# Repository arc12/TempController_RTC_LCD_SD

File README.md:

Multiple DS18B20 temperature sensors with LCD display, SD card logging, remote control via Serial/USB, real time clock, and up to control an output.

Intended for compilation in Atmel Studio and deployment on a custom ATMega328 based circuit. See source code for notes on use with Arduino IDE.

Various library dependencies not in github yet (will be separate repos). See *.atsln

The idea of this is to have 3 temp sensors: one in a well inside the beer (5 gallon bucket), one inside a ply-wood box (contains a heater pad and the bucket), and one in the outside room. Logging temperature for all three will give an idea of the thermal properties of the assembly and of the heat produced by fermentation. In the first instance, a very simple control rule will be used, taking only the temperature from in the wort and testing for a min temperature with fixed hysteresis. See the MS Word Doc.

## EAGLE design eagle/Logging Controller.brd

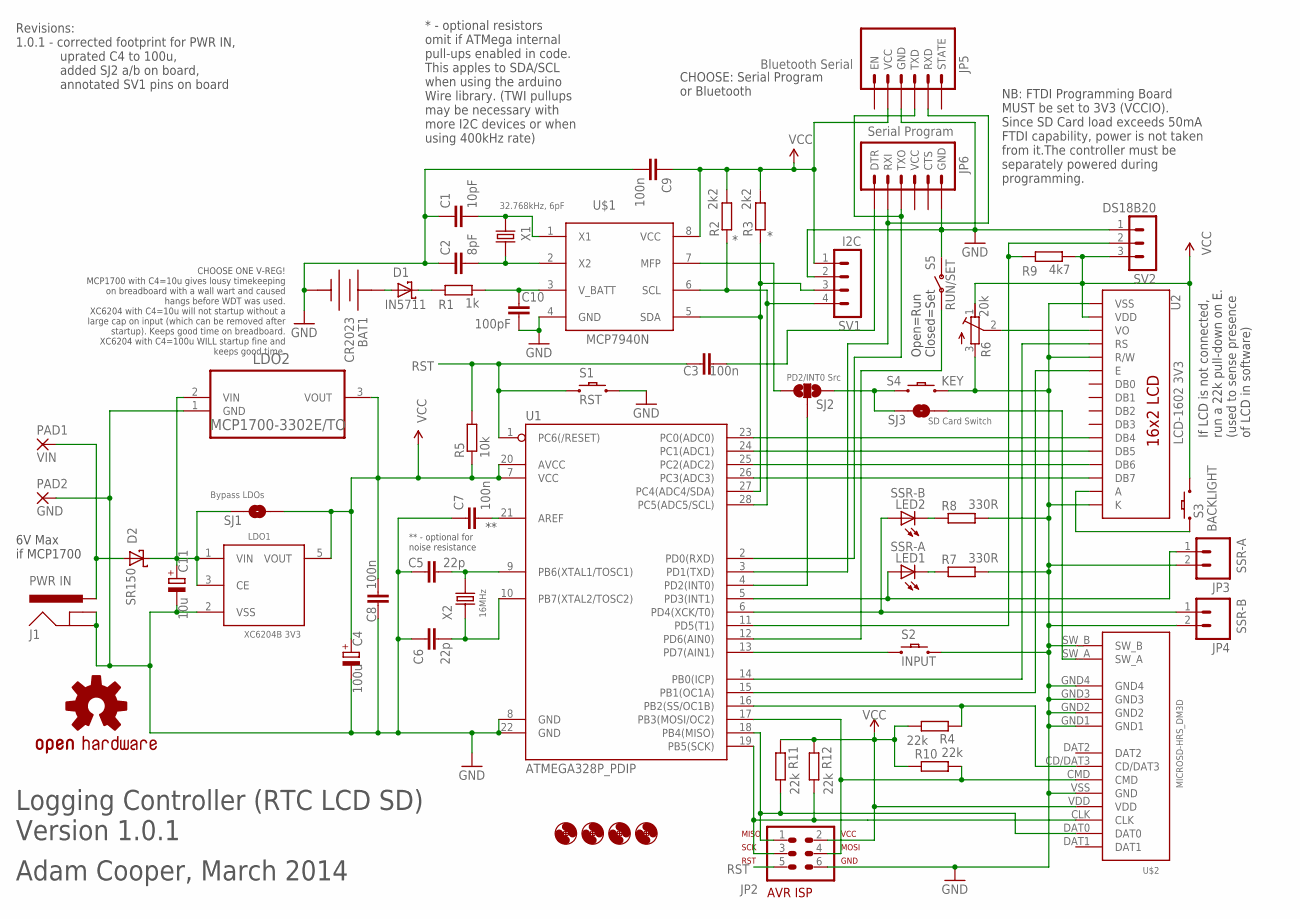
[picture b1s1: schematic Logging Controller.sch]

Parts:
BAT1: CR2023; KEYSTONE3003
C1: 10pF; C025-024X044
C2: 8pF; C025-024X044
C3, C7, C8, C9: 100n; C025-024X044
C4: 100u; E2,5-5
C5, C6: 22p; C025-024X044
C10: 100pF; C025-024X044
C11: 10u; E2,5-5
D1: IN5711; DO35-7
D2: SR150; DO-41
H1, H2, H3, H4: MOUNT-HOLE3.0_REDUCED; 3,0
J1: PWR IN; POWER_JACK_SLOT2
JP2: AVR-ISP; AVR-ISP-6
JP3: SSR-A; 1X02
JP4: SSR-B; 1X02
JP5: Bluetooth Serial; BT_MOD_ROUND
JP6: Serial Program; 1X06
LDO1: XC6204B 3V3; SOT23-5
LDO2: MCP1700-3302E/TO; TO127P254X495-3
LED1: SSR-A; LED5MM
LED2: SSR-B; LED5MM
LOGO1: OSHW-LOGOS; OSHW-LOGO-S
PAD1: VIN; 2,54/1,1
PAD2: GND; 2,54/1,1
R1: 1k; 0204/7
R2, R3: 2k2; 0204/7
R4, R10, R11, R12: 22k; 0204/7
R5: 10k; 0204/7
R6: 20k; RTRIMT93YB
R7, R8: 330R; 0204/7
R9: 4k7; 0204/7
S1: RST; TACTILE-PTH
S2: INPUT; OFF_BOARD_SPST
S3: BACKLIGHT; OFF_BOARD_SPST
S4: KEY; OFF_BOARD_SPST
S5: RUN/SET; SWITCH-SPST-OFFBOARD
SJ1: Bypass LDOs; SJ_2S-NO
SJ2: PD2/INT0 Src; SJ_3
SJ3: SD Card Switch; SJ_2S-NO
SV1: I2C; MA04-1
SV2: DS18B20; MA03-1
U1: ATMEGA328P_PDIP; DIL28-3@1
U2: LCD-1602 3V3; LCD-16X2_NOSILK
U$1: MCP7940N; DIL08
U$2: MICROSD-HRS_DM3D; DM3D
X1: 32.768kHz, 6pF; TC26H
X2: 16MHz; HC49U-V

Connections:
GND: BAT1.NEG, C1.1, C2.1, C4.-, C5.1, C6.1, C7.1, C8.1, C9.2, C10.1, C11.-, J1.GND, J1.GND2 (GNDBREAK), JP2.6, JP3.2, JP4.2, JP5.4 (GND), JP6.6 (GND), LDO1.2 (VSS), LDO2.1 (GND), PAD2.1, R6.3 (E), R7.2, R8.2, S1.3 (2), S2.P$2 (2), S4.P$2 (2), S5.1 (O), SV1.2, SV2.1, U1.8 (GND), U1.22 (GND), U2.1 (VSS), U2.5 (R/W), U2.16 (K), U$1.4 (GND), U$2.GND1, U$2.GND2, U$2.GND3, U$2.GND4, U$2.SW_B, U$2.VSS (GND)
unnamed: R9.1, SV2.2, U1.11 (PD5(T1))
unnamed: R4.1, U1.16 (PB2(SS/OC1B)), U$2.CD/DAT3
unnamed: U1.14 (PB0(ICP)), U2.4 (RS)
unnamed: U1.15 (PB1(OC1A)), U2.6 (E)
unnamed: U1.23 (PC0(ADC0)), U2.11 (DB4)
unnamed: U1.24 (PC1(ADC1)), U2.12 (DB5)
unnamed: U1.25 (PC2(ADC2)), U2.13 (DB6)
unnamed: U1.26 (PC3(ADC3)), U2.14 (DB7)
unnamed: S3.P$1 (1), U2.15 (A)
unnamed: S2.P$1 (1), U1.13 (PD7(AIN1))
unnamed: S5.2, U1.12 (PD6(AIN0))
unnamed: JP4.1, LED2.A, U1.6 (PD4(XCK/T0))
unnamed: JP3.1, LED1.A, U1.5 (PD3(INT1))
unnamed: LED2.K (C), R8.1
unnamed: LED1.K (C), R7.1
unnamed: S4.P$1 (1), SJ2.3, SJ3.1
unnamed: SJ2.2, U1.4 (PD2(INT0))
unnamed: R6.2 (S), U2.3 (VO)
unnamed: SJ3.2, U$2.SW_A
unnamed: SJ2.1, U$1.7 (MFP)
unnamed: JP5.3 (TXD), JP6.3 (TXO), U1.2 (PD0(RXD))
unnamed: JP2.4, R10.2, U1.17 (PB3(MOSI/OC2)), U$2.CMD
unnamed: JP2.1, R11.2, U1.18 (PB4(MISO)), U$2.DAT0
unnamed: JP5.2 (RXD), JP6.2 (RXI), U1.3 (PD1(TXD))
unnamed: R3.1, SV1.3, U1.27 (PC4(ADC4/SDA)), U$1.5 (SDA)
unnamed: R2.1, SV1.4, U1.28 (PC5(ADC5/SCL)), U$1.6 (SCL)
unnamed: C1.2, U$1.1 (X1), X1.2
unnamed: C2.2, U$1.2 (X2), X1.1
unnamed: BAT1.POS, BAT1.POS1 (POS), D1.A
unnamed: D1.C, R1.1
unnamed: C10.2, R1.2, U$1.3 (V_BATT)
unnamed: C11.+, D2.C, LDO1.1 (VIN), LDO1.3 (CE), LDO2.2 (VIN), SJ1.1
unnamed: D2.A, J1.POS (PWR), PAD1.1
unnamed: C5.2, U1.9 (PB6(XTAL1/TOSC1)), X2.2
unnamed: C3.2, JP6.1 (DTR)
unnamed: C6.2, U1.10 (PB7(XTAL2/TOSC2)), X2.1
unnamed: JP2.3, R12.2, U1.19 (PB5(SCK)), U$2.CLK
unnamed: C7.2, U1.21 (AREF)
RST: C3.1, JP2.5, R5.2, S1.1, U1.1 (PC6(/RESET))
VCC: C4.+, C8.2, C9.1, JP2.2, JP5.5 (VCC), LDO1.5 (VOUT), LDO2.3 (VOUT), R2.2, R3.2, R4.2, R5.1, R6.1 (A), R9.2, R10.1, R11.1, R12.1, S3.P$2 (2), SJ1.2, SV1.1, SV2.3, U1.7 (VCC), U1.20 (AVCC), U2.2 (VDD), U$1.8 (VCC), U$2.VDD

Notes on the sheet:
Adam Cooper, March 2014
Logging Controller (RTC LCD SD) Version 1.0.1
Open=Run Closed=Set
* - optional resistors omit if ATMega internal pull-ups enabled in code. This apples to SDA/SCL when using the arduino Wire library. (TWI pullups may be necessary with more I2C devices or when using 400kHz rate)
6V Max if MCP1700
** - optional for noise resistance
NB: FTDI Programming Board MUST be set to 3V3 (VCCIO). Since SD Card load exceeds 50mA FTDI capability, power is not taken from it.The controller must be separately powered during programming.
CHOOSE ONE V-REG! MCP1700 with C4=10u gives lousy timekeeping on breadboard with a wall wart and caused hangs before WDT was used. XC6204 with C4=10u will not startup without a large cap on input (which can be removed after startup). Keeps good time on breadboard. XC6204 with C4=100u WILL startup f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
If LCD is not connected, run a 22k pull-down on E. (used to sense presence of LCD in software)
CHOOSE: Serial Program or Bluetooth
Revisions: 1.0.1 - corrected footprint for PWR IN, uprated C4 to 100u, added SJ2 a/b on board, annotated SV1 pins on board

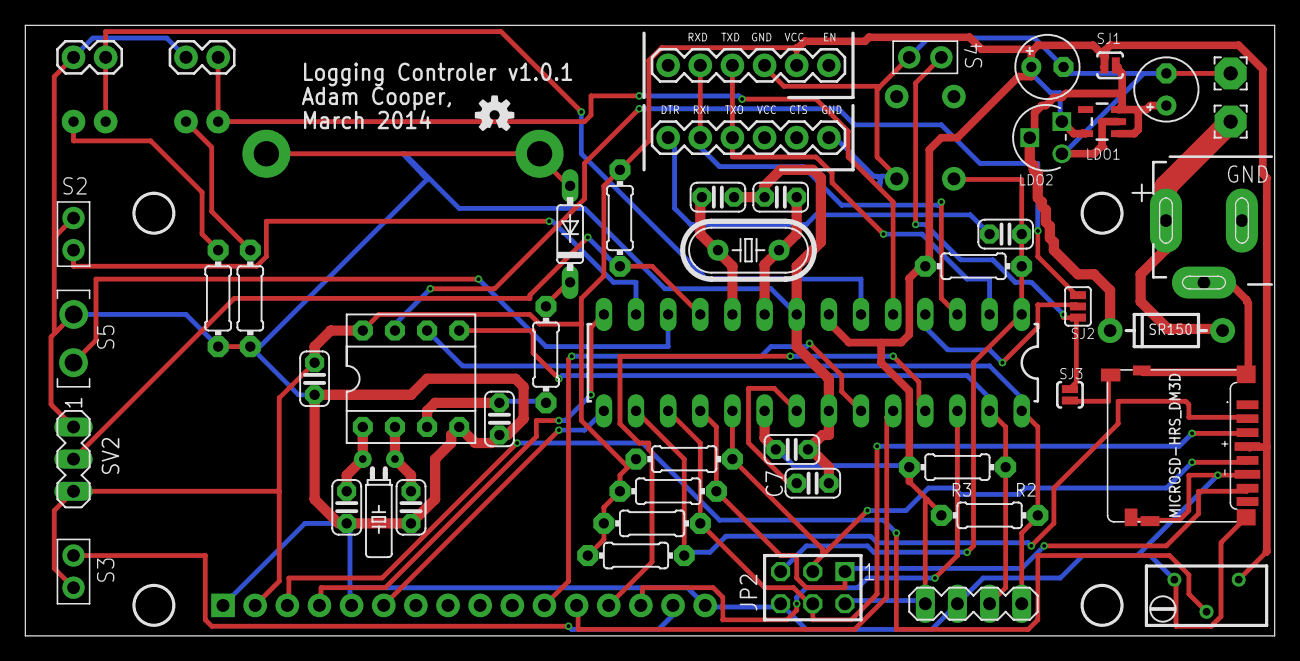
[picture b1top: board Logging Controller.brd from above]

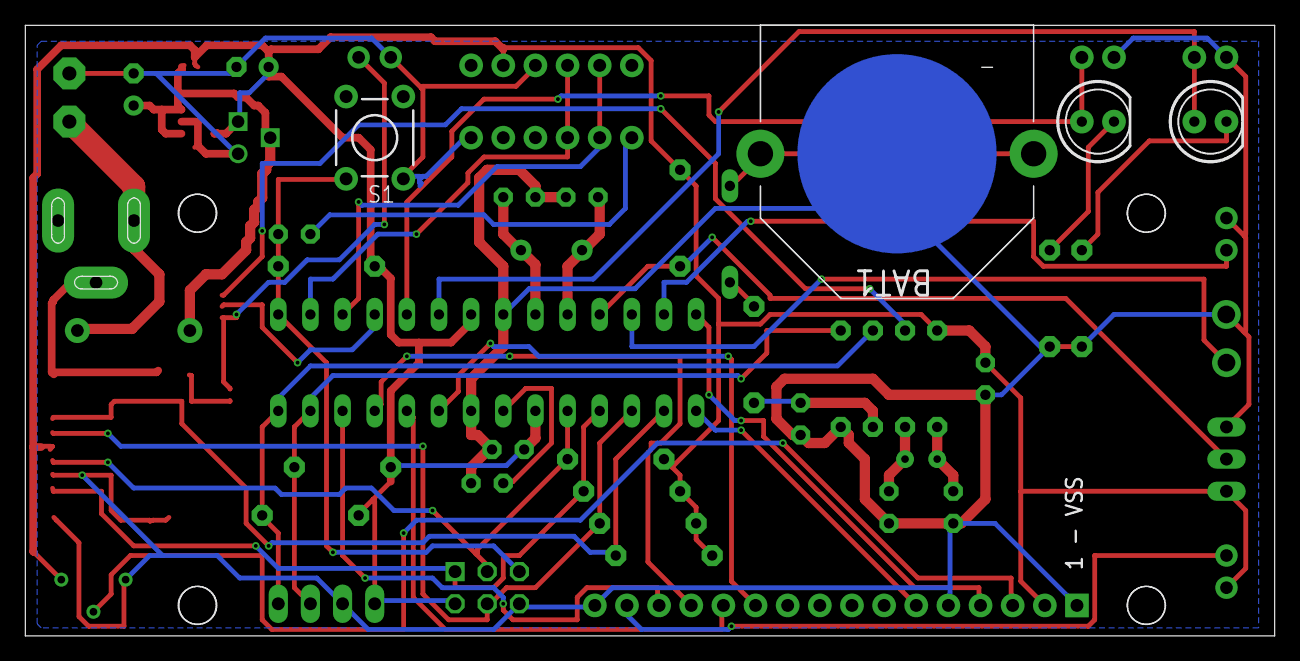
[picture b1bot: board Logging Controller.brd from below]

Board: 2 copper layers, 98.7 x 48.2 mm, 59 parts (5 on the bottom side), 41 nets.

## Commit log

2014-03-23 v1.0.0 candidate 1
2014-03-23 readme
2014-03-23 add atmel studio solution
2014-03-23 draft documentation
2014-03-23 add eagle backup files and atmel studio trash
2014-03-23 dates corrected
2014-03-23 more info
2014-03-23 board layout to be refined
2014-03-23 tidied silk, adjusted some positions. Thick traces and ground fill
2014-03-23 Gerbers as per Seeed CAM file plus board outline and inclusion of values in silk
2014-04-04 eagle added
2014-04-04 add: 1) use output B to signal over-shoot; 2) in run mode, pressing the button now causes display of all temp sensor values
2014-04-04 minor rev
2014-04-04 added note on application
2014-04-10 oops
2014-04-12 v1.0.1 revision, esp fix power in pinout.
2014-04-12 Changes to SD card behaviour, and cleanup SD card text and outB info
2014-04-12 add warning LED in setup mode. Better SD card insert/remove behaviour. Some cosmetic display changes.
2014-04-17 changed behaviour of *TEMP command
2014-04-17 changed behaviour of *TEMP command. Made time be updated in setup mode. set SPI to floating condition on SD fail or remove.

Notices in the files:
parts and their libraries:
SparkFun-Aesthetics: Licensing: CC v3.0 Share-Alike You are welcome to use this library for commercial purposes.
